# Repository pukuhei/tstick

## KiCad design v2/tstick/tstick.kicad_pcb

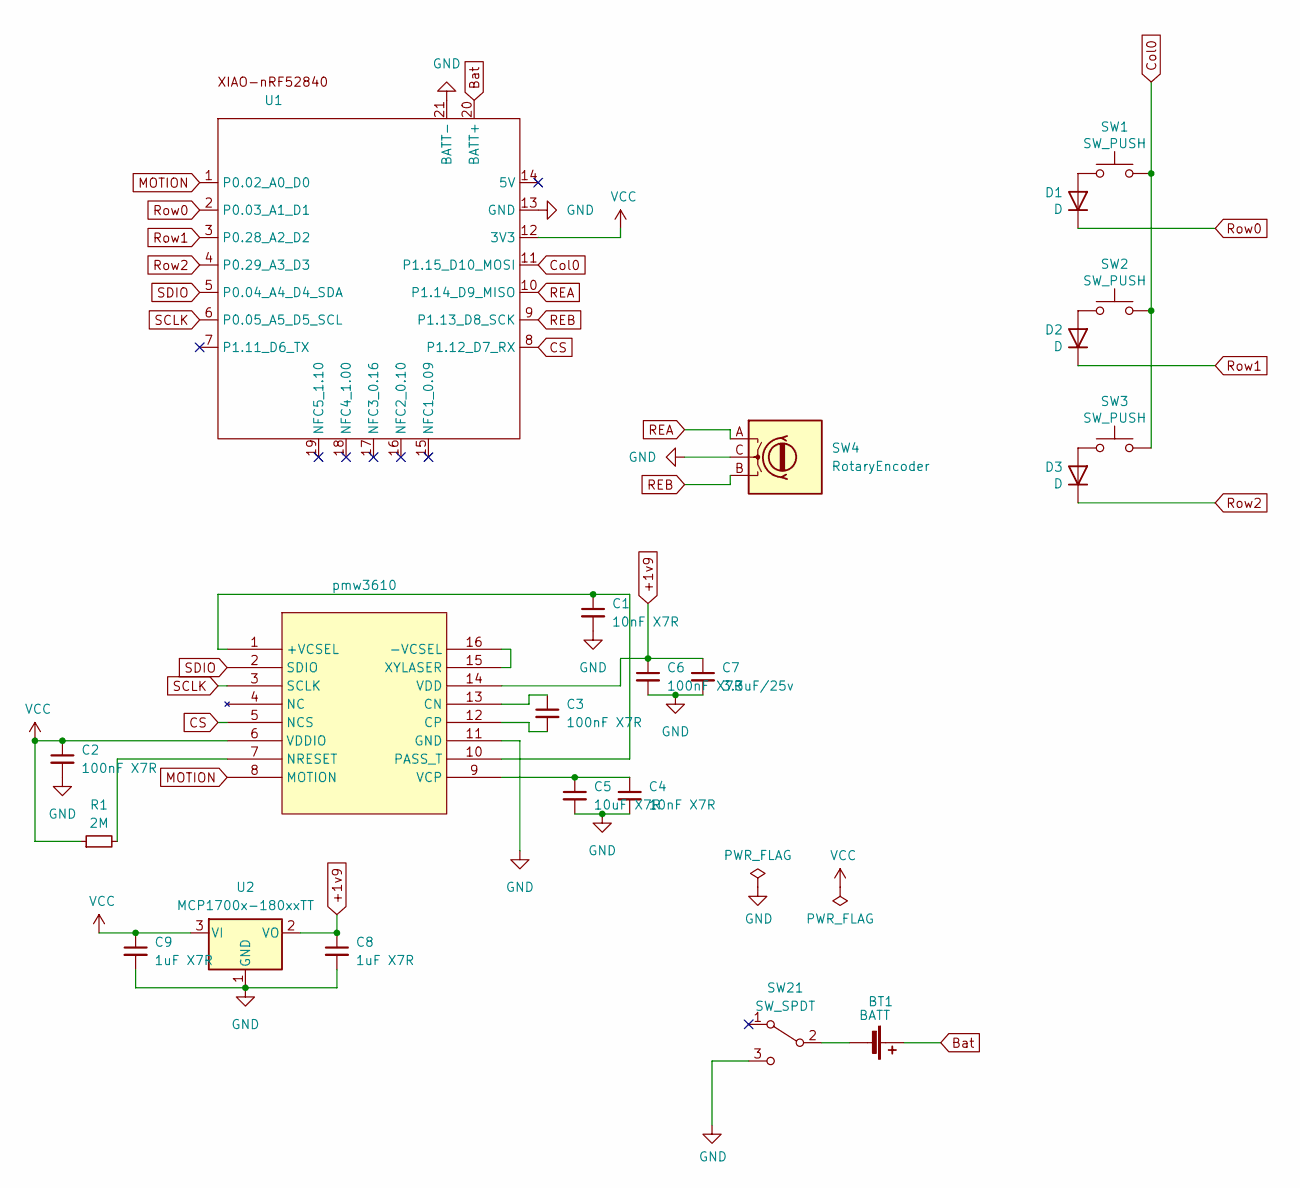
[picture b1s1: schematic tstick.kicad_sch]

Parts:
BT1: BATT; JST_S2B-PH-SM4-TB
C1, C4: 10nF X7R; C_0603_1608Metric
C2, C3, C6: 100nF X7R; C_0603_1608Metric
C5: 10uF X7R; C_0603_1608Metric
C7: 3.3uF/25v; C_0603_1608Metric
C8, C9: 1uF X7R; C_0603_1608Metric
D1, D2, D3: D; Diode_TH_SMD
R1: 2M; C_0603_1608Metric
SW1, SW2, SW3: SW_PUSH; MX_Choc_v1v2_Hotswap_1u
SW4: RotaryEncoder; RotaryEncoder_EC12E
SW21: SW_SPDT; TGSW_MSK-12D19
U1: XIAO_nRF52840_wBAT_wNFC_1
U2: MCP1700x-180xxTT; SOT-23
pmw3610: PMW3610DM-SUDU

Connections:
+1v9: C6.1, C7.1, C8.1, U2.2 (VO), pmw3610.14 (VDD)
Bat: BT1.1 (+), U1.20 (BATT+)
CS: U1.8 (P1.12_D7_RX), pmw3610.5 (NCS)
Col0: SW1.1, SW2.1, SW3.1, U1.11 (P1.15_D10_MOSI)
GND: C1.2, C2.2, C4.2, C5.2, C6.2, C7.2, C8.2, C9.2, SW4.C, SW21.3 (C), U1.13 (GND), U1.21 (BATT-), U2.1 (GND), pmw3610.11 (GND)
MOTION: U1.1 (P0.02_A0_D0), pmw3610.8 (MOTION)
unnamed: BT1.2 (-), SW21.2 (B)
unnamed: D1.2 (A), SW1.2
unnamed: D2.2 (A), SW2.2
unnamed: D3.2 (A), SW3.2
unnamed: C1.1, pmw3610.1 (+VCSEL), pmw3610.10 (PASS_T)
unnamed: pmw3610.15 (XYLASER), pmw3610.16 (-VCSEL)
unnamed: C3.1, pmw3610.13 (CN)
unnamed: C3.2, pmw3610.12 (CP)
unnamed: R1.2, pmw3610.7 (NRESET)
unnamed: C4.1, C5.1, pmw3610.9 (VCP)
REA: SW4.A, U1.10 (P1.14_D9_MISO)
REB: SW4.B, U1.9 (P1.13_D8_SCK)
Row0: D1.1 (K), U1.2 (P0.03_A1_D1)
Row1: D2.1 (K), U1.3 (P0.28_A2_D2)
Row2: D3.1 (K), U1.4 (P0.29_A3_D3)
SCLK: U1.6 (P0.05_A5_D5_SCL), pmw3610.3 (SCLK)
SDIO: U1.5 (P0.04_A4_D4_SDA), pmw3610.2 (SDIO)
VCC: C2.1, C9.1, R1.1, U1.12 (3V3), U2.3 (VI), pmw3610.6 (VDDIO)

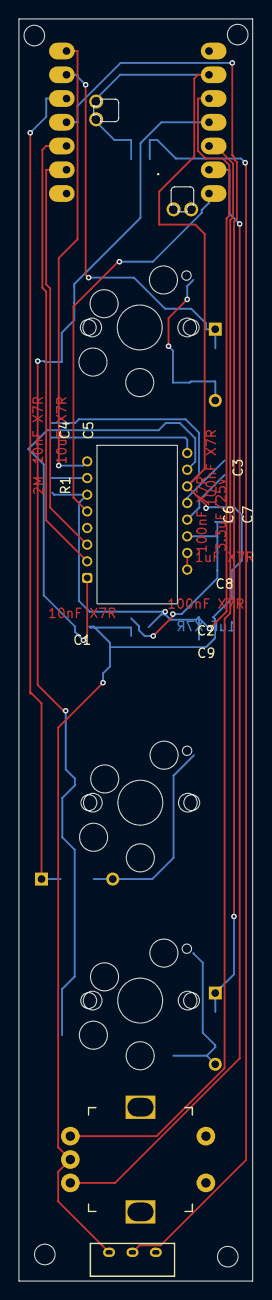
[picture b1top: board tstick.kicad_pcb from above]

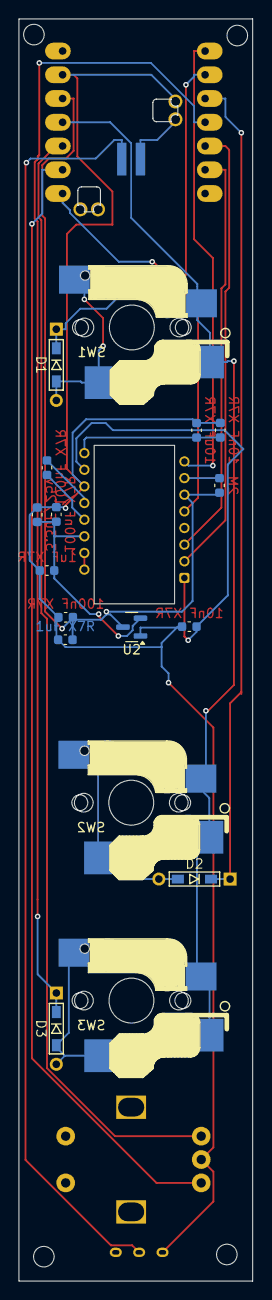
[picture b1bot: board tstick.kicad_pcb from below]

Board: 2 copper layers, 25.0 x 135.0 mm, 26 parts (12 on the bottom side), 24 nets.

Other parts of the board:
Ref**: Val**; m2_Screw_Hole
Ref**#2, Ref**#3, Ref**#4: Val**; m2_Screw_Hole

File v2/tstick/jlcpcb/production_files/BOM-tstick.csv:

Comment,Designator,Footprint,LCSC,Quantity
100nF X7R,"C2,C3,C6",C_0603_1608Metric,C14663,3
MCP1700x-180xxTT,U2,SOT-23,C20627192,1
2M,R1,C_0603_1608Metric,C22976,1
1uF X7R,"C8,C9",C_0603_1608Metric,C28323,2
3.3uF/25v,C7,C_0603_1608Metric,C342962,1
10nF X7R,"C1,C4",C_0603_1608Metric,C57112,2
10uF X7R,C5,C_0603_1608Metric,C96446,1
BATT,BT1,JST_S2B-PH-SM4-TB,,1
~,U1,XIAO_nRF52840_wBAT_wNFC_1,,1
SW_SPDT,SW21,TGSW_MSK-12D19,,1
RotaryEncoder,SW4,RotaryEncoder_EC12E,,1
SW_PUSH,SW3,MX_Choc_v1v2_Hotswap_1u,,1
SW_PUSH,SW2,MX_Choc_v1v2_Hotswap_1u,,1
SW_PUSH,SW1,MX_Choc_v1v2_Hotswap_1u,,1
~,pmw3610,PMW3610DM-SUDU,,1
D,D3,Diode_TH_SMD,,1
D,D2,Diode_TH_SMD,,1
D,D1,Diode_TH_SMD,,1

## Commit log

2025-11-06 first
2025-11-06 25mmボールが入るように修正
2025-11-19 test_keymap
2025-11-20 test_module
2025-11-20 fixencorder
2025-11-21 bt変更を追加
